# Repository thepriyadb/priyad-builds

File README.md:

* RoverX: Designed a multi-sensor PCB and developed STM32 firmware for real-time environmental telemetry. Along with NPK sensor integration.
* Ctrl+Sea – Water Quality Monitoring: Designed an embedded system for real-time monitoring of pH, salinity, turbidity, and temperature.
* ScalarArc – Smart Suspension Module: Developed a sensorless estimation model and MLP for actuator load and position prediction.
* Braille-to-Text System: Created an assistive embedded system converting Braille inputs into real-time text with audio feedback.
* NPK Soil Sensor (Ongoing): Developing a low-cost soil nutrient sensing system with improved accuracy across moisture conditions.
* Universal Encoder Interface (Ongoing): Designing a modular interface to standardize encoder data for robotics motion control.

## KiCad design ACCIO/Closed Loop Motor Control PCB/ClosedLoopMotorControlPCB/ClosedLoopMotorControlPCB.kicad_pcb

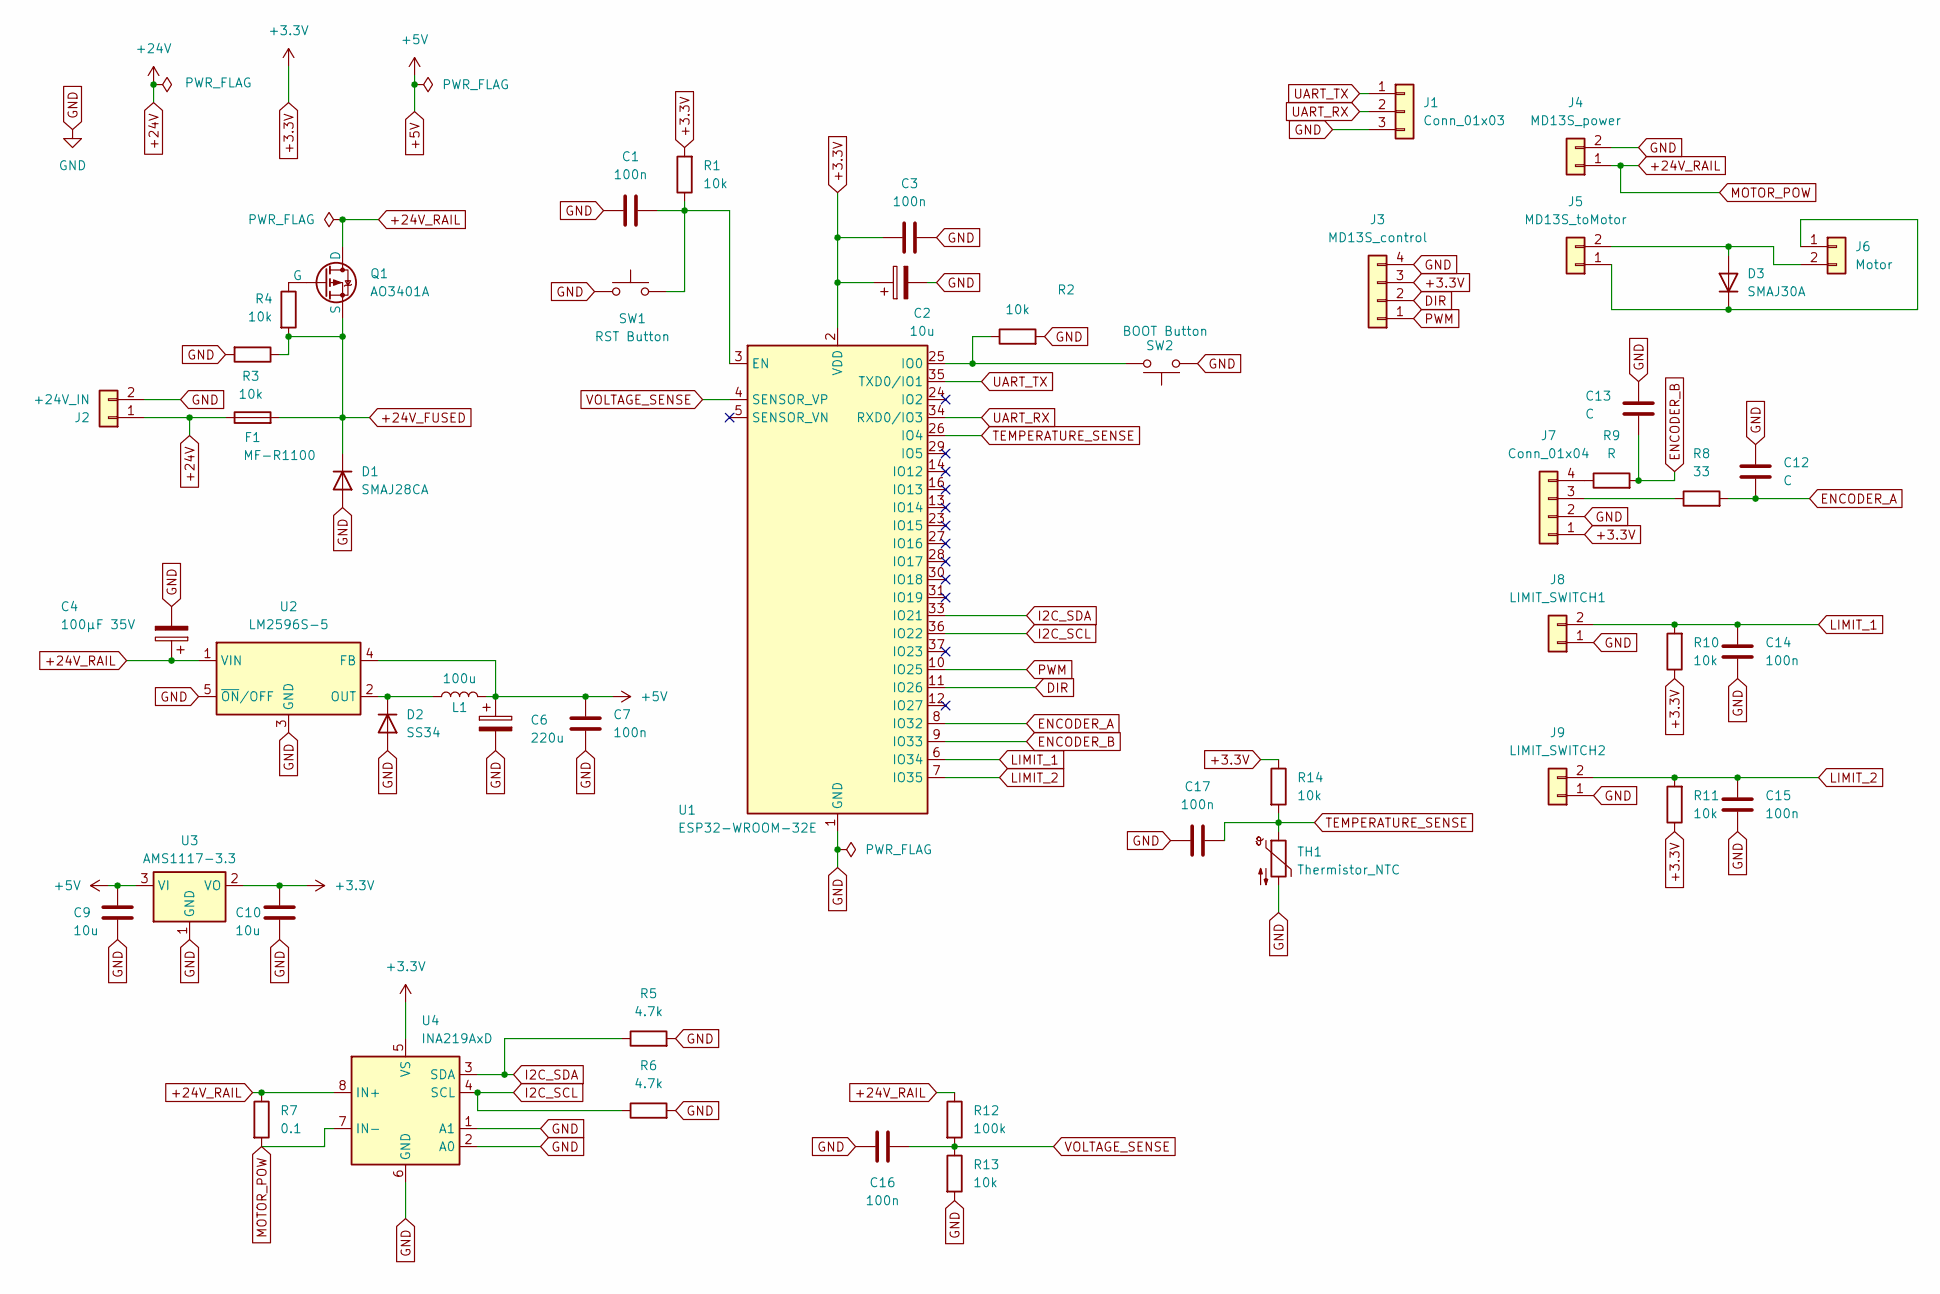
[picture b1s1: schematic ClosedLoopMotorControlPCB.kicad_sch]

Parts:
C1, C3, C7, C14, C15, C16, C17: 100n; C_0805_2012Metric
C2, C9, C10: 10u; C_0805_2012Metric
C4: 100µF 35V; CP_Radial_D10.0mm_P5.00mm
C6: 220u; CP_Radial_D8.0mm_P3.50mm
C12, C13: C; C_0805_2012Metric
D1: SMAJ28CA; D_SMA
D2: SS34; D_SMA
D3: SMAJ30A; D_SMA
F1: MF-R1100; Fuse_1812_4532Metric
J1: Conn_01x03; PinHeader_1x03_P2.54mm_Vertical
J2: +24V_IN; AMASS_XT60-F_1x02_P7.20mm_Vertical
J3: MD13S_control; JST_PH_B4B-PH-K_1x04_P2.00mm_Vertical
J4: MD13S_power; AMASS_XT30U-F_1x02_P5.0mm_Vertical
J5: MD13S_toMotor; AMASS_XT30U-F_1x02_P5.0mm_Vertical
J6: Motor; AMASS_XT60-F_1x02_P7.20mm_Vertical
J7: Conn_01x04; JST_PH_B4B-PH-K_1x04_P2.00mm_Vertical
J8: LIMIT_SWITCH1; PinHeader_1x02_P2.54mm_Vertical
J9: LIMIT_SWITCH2; PinHeader_1x02_P2.54mm_Vertical
L1: 100u; L_7.3x7.3_H3.5
Q1: AO3401A; SOT-23
R1, R2, R3, R4, R10, R11, R13, R14: 10k; R_0805_2012Metric
R5, R6: 4.7k; R_0805_2012Metric
R7: 0.1; R_2512_6332Metric
R8: 33; R_0805_2012Metric
R9: R; R_0805_2012Metric
R12: 100k; R_0805_2012Metric
SW1: RST Button; SW_Tactile_SPST_Angled_PTS645Vx31-2LFS
SW2: BOOT Button; SW_Tactile_SPST_Angled_PTS645Vx31-2LFS
TH1: Thermistor_NTC; R_Axial_DIN0207_L6.3mm_D2.5mm_P7.62mm_Horizontal
U1: ESP32-WROOM-32E
U2: LM2596S-5; TO-263-5_TabPin3
U3: AMS1117-3.3; SOT-223-3_TabPin2
U4: INA219AxD; SOIC-8_3.9x4.9mm_P1.27mm

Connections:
+3.3V: C2.1, C3.1, C10.1, J3.3, J7.1, R1.2, R10.1, R11.1, R14.1, U1.2 (VDD), U3.2 (VO), U4.5 (VS)
+5V: C6.1, C7.1, C9.1, L1.2, U2.4 (FB), U3.3 (VI)
+24V: F1.1, J2.1
+24V_FUSED: D1.1 (K), F1.2, Q1.3 (S), R3.1, R4.2
+24V_RAIL: C4.1, J4.1, Q1.1 (D), R7.1, R7.2, R12.1, U2.1 (VIN), U4.7 (IN-), U4.8 (IN+)
DIR: J3.2, U1.11 (IO26)
ENCODER_A: C12.2, R8.2, U1.8 (IO32)
ENCODER_B: C13.2, R9.2, U1.9 (IO33)
GND: C1.1, C2.2, C3.2, C4.2, C6.2, C7.2, C9.2, C10.2, C12.1, C13.1, C14.2, C15.2, C16.1, C17.1, D1.2 (A), D2.2 (A), J1.3, J2.2, J3.4, J4.2, J7.2, J8.1, J9.1, R2.2, R3.2, R5.2, R6.2, R13.2, SW1.1, SW2.1, TH1.2, U1.1 (GND), U1.15 (GND), U1.38 (GND), U1.39 (GND), U2.3 (GND), U2.5 (~ON/OFF), U3.1 (GND), U4.1 (A1), U4.2 (A0), U4.6 (GND)
I2C_SCL: R6.1, U1.36 (IO22), U4.4 (SCL)
I2C_SDA: R5.1, U1.33 (IO21), U4.3 (SDA)
LIMIT_1: C14.1, J8.2, R10.2, U1.6 (IO34)
LIMIT_2: C15.1, J9.2, R11.2, U1.7 (IO35)
unnamed: D2.1 (K), L1.1, U2.2 (OUT)
unnamed: D3.2 (A), J5.2, J6.2
unnamed: D3.1 (K), J5.1, J6.1
unnamed: J7.3, R8.1
unnamed: J7.4, R9.1
unnamed: Q1.2 (G), R4.1
unnamed: C1.2, R1.1, SW1.2, U1.3 (EN)
unnamed: R2.1, SW2.2, U1.25 (IO0)
PWM: J3.1, U1.10 (IO25)
TEMPERATURE_SENSE: C17.2, R14.2, TH1.1, U1.26 (IO4)
UART_RX: J1.2, U1.34 (RXD0/IO3)
UART_TX: J1.1, U1.35 (TXD0/IO1)
VOLTAGE_SENSE: C16.2, R12.2, R13.1, U1.4 (SENSOR_VP)

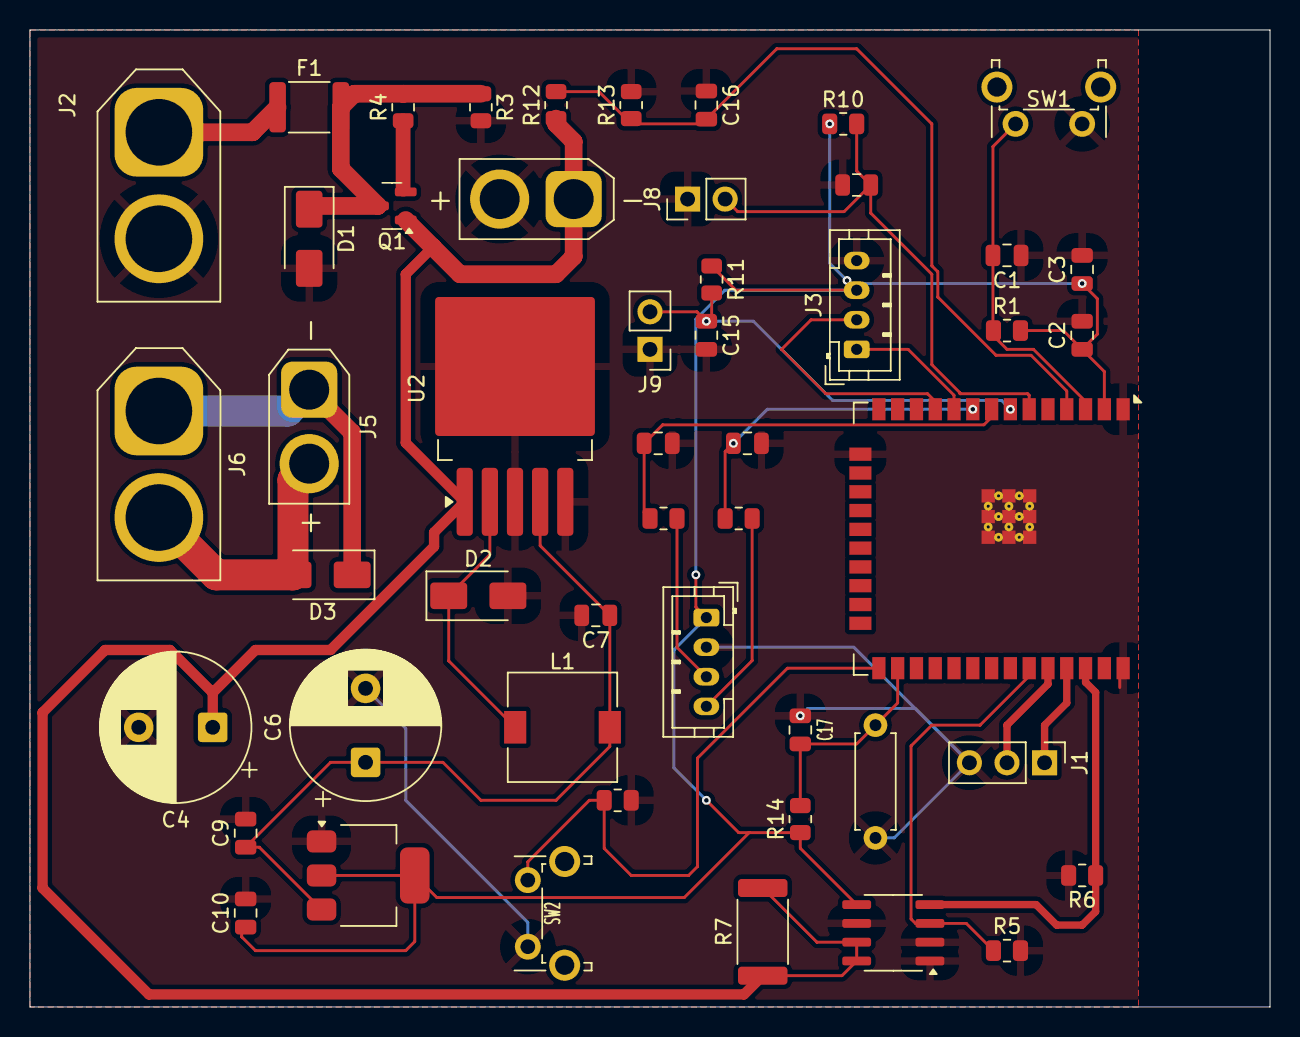
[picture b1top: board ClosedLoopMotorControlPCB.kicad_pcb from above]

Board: 2 copper layers, 83.8 x 66.0 mm, 50 parts (0 on the bottom side), 26 nets.

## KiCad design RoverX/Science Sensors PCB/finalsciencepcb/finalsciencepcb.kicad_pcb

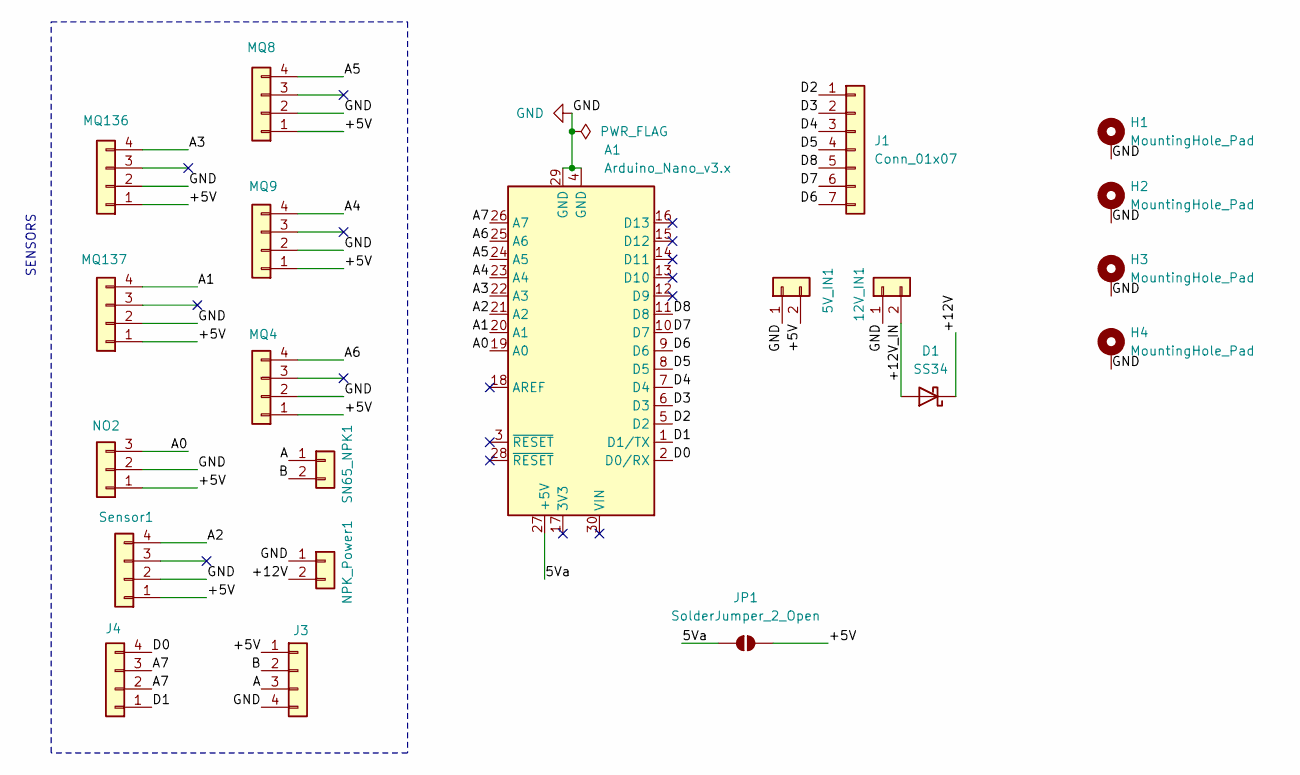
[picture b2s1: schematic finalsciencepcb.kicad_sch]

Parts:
5V_IN1, 12V_IN1: Conn_01x02; AMASS_XT60-F_1x02_P7.20mm_Vertical
A1: Arduino_Nano_v3.x; Arduino_Nano
D1: SS34; D_SMA
H1, H2, H3, H4: MountingHole_Pad; MountingHole_4mm_Pad
J1: Conn_01x07; JST_XA_B07B-XASK-1_1x07_P2.50mm_Vertical
J3, J4: Conn_01x04; PinHeader_1x04_P2.54mm_Vertical
JP1: SolderJumper_2_Open; SolderJumper-2_P1.3mm_Open_Pad1.0x1.5mm
MQ4, MQ8, MQ9, MQ136, MQ137: Conn_01x04; PinHeader_1x04_P2.54mm_Vertical
NO2: Conn_01x03; PinHeader_1x03_P2.54mm_Vertical
NPK_Power1: Conn_01x02; AMASS_XT30U-F_1x02_P5.0mm_Vertical
SN65_NPK1: Conn_01x02; AMASS_XT30U-F_1x02_P5.0mm_Vertical
Sensor1: Conn_01x04; PinHeader_1x04_P2.54mm_Vertical

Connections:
/5Va: A1.27 (+5V), JP1.1 (A)
/+5V: 5V_IN1.2, J3.1, JP1.2 (B), MQ4.1, MQ8.1, MQ9.1, MQ136.1, MQ137.1, NO2.1, Sensor1.1
/+12V: D1.1 (K), NPK_Power1.2
/+12V_IN: 12V_IN1.2, D1.2 (A)
/A: J3.3, SN65_NPK1.1
/A0: A1.19 (A0), NO2.3
/A1: A1.20 (A1), MQ137.4
/A2: A1.21 (A2), Sensor1.4
/A3: A1.22 (A3), MQ136.4
/A4: A1.23 (A4), MQ9.4
/A5: A1.24 (A5), MQ8.4
/A6: A1.25 (A6), MQ4.4
/A7: A1.26 (A7), J4.2, J4.3
/B: J3.2, SN65_NPK1.2
/D0: A1.2 (D0/RX), J4.4
/D1: A1.1 (D1/TX), J4.1
/D2: A1.5 (D2), J1.1
/D3: A1.6 (D3), J1.2
/D4: A1.7 (D4), J1.3
/D5: A1.8 (D5), J1.4
/D6: A1.9 (D6), J1.7
/D7: A1.10 (D7), J1.6
/D8: A1.11 (D8), J1.5
GND: 5V_IN1.1, 12V_IN1.1, A1.4 (GND), A1.29 (GND), H1.1, H2.1, H3.1, H4.1, J3.4, MQ4.2, MQ8.2, MQ9.2, MQ136.2, MQ137.2, NO2.2, NPK_Power1.1, Sensor1.2

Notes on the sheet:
SENSORS

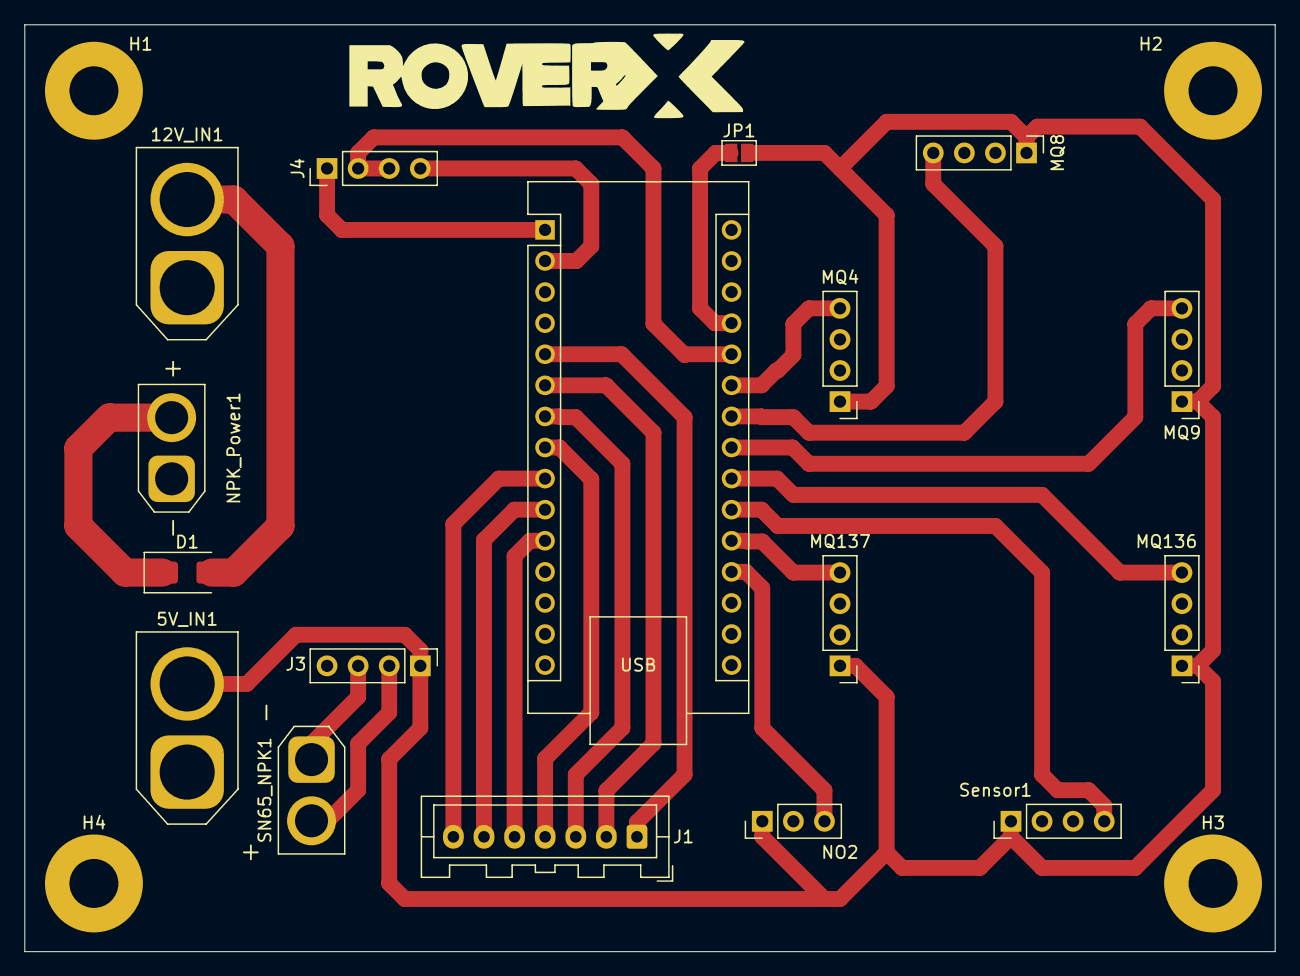
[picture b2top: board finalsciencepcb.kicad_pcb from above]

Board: 2 copper layers, 102.2 x 75.7 mm, 21 parts (0 on the bottom side), 24 nets.

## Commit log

2026-04-07 ScalarArc - priyad
    ScalarArc
2026-04-07 braille-to-text - priyad
    braille-to-text
2026-04-07 roverx - priyad
    roverx - priya d
2026-04-07 Priya D - Projecrs
2026-04-07 readme - priyad
2026-04-20 accio task upload
2026-04-20 accio task
2026-04-20 accio task update
